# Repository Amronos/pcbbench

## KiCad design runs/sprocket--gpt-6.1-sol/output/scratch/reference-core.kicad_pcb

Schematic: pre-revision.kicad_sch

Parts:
C1, C18, C20: 1 µF; C_0402_1005Metric; MPN GRM155R61A105KE15D
C2, C6, C7, C9, C10, C11, C12, C13, C14, C15, C16, C17, C19, C25, C29, C33, C34: 100 nF; C_0402_1005Metric; MPN GRM155R71C104KA88D
C3, C4: 15 pF; C_0402_1005Metric; MPN GRM1555C1H150JA01D
C5, C21, C22, C31, C32: 4.7 µF; C_0603_1608Metric; MPN GRM188R61A475KE15D
C8: 4.7 µF; C_0402_1005Metric; MPN GRM155R60J475ME87D
C23, C24, C28, C30: 10 µF; C_0805_2012Metric; MPN GRM21BR61A106KE19L
C26, C27: 22 µF; C_0805_2012Metric; MPN GRM21BR60J226ME39L
D1: USB ESD; SOT-23-6; MPN USBLC6-2SC6
D2: RGB; LED_WS2812B-2020_PLCC4_2.0x2.0mm; MPN WS2812C-2020-V6
J1: USB-C; USB_C_Receptacle_HRO_TYPE-C-31-M-12; MPN TYPE-C-31-M-12
J2: microSD SPI; microSD_HC_Hirose_DM3AT-SF-PEJM5; MPN DM3AT-SF-PEJM5
J3: LiPo + NTC; JST_PH_S3B-PH-SM4-TB_1x03-1MP_P2.00mm_Horizontal; MPN S3B-PH-SM4-TB(LF)(SN)
J4: Qwiic / STEMMA QT; JST_SH_BM04B-SRSS-TB_1x04-1MP_P1.00mm_Vertical; MPN BM04B-SRSS-TB(LF)(SN)
J5: GPIO expansion; PinHeader_2x10_P2.54mm_Vertical; MPN 61302021121
J6: SWD; PinHeader_1x04_P2.54mm_Vertical; MPN 61300411121
L1: 2.2 µH; L_1812_4532Metric; MPN LQH44PN2R2MP0L
L2: 3.3 µH; L_Abracon_AOTA-B201610S; MPN AOTA-B201610S3R3-101-T
Q1: Battery sense gate; SOT-23; MPN BSS84
Q2: Sense enable; SOT-23; MPN 2N7002
R1, R2: 5.1 kΩ; R_0402_1005Metric; MPN RC0402FR-075K1L
R3, R4: 27 Ω; R_0402_1005Metric; MPN RC0402FR-0727RL
R5, R6, R8, R9, R10, R11, R12, R17, R18, R26, R27, R28, R29, R30, R31: 10 kΩ; R_0402_1005Metric; MPN RC0402FR-0710KL
R7, R25, R33, R34: 1 kΩ; R_0402_1005Metric; MPN RC0402FR-071KL
R13: 2.94 kΩ; R_0402_1005Metric; MPN RC0402FR-072K94L
R14: 3.83 kΩ; R_0402_1005Metric; MPN RC0402FR-073K83L
R15: 46.4 kΩ; R_0402_1005Metric; MPN RC0402FR-0746K4L
R16: 2.0 kΩ; R_0402_1005Metric; MPN RC0402FR-072KL
R19, R20, R23, R24, R35, R36: 100 kΩ; R_0402_1005Metric; MPN RC0402FR-07100KL
R21, R22: 4.7 kΩ; R_0402_1005Metric; MPN RC0402FR-074K7L
R32: 33 Ω; R_0402_1005Metric; MPN RC0402FR-0733RL
SW1: BOOT_SW; SW_SPST_B3U-1000P; MPN B3U-1000P
SW2: RUN; SW_SPST_B3U-1000P; MPN B3U-1000P
SW3: RADIO_BOOT; SW_SPST_B3U-1000P; MPN B3U-1000P
SW4: RADIO_EN; SW_SPST_B3U-1000P; MPN B3U-1000P
U1: RP2350A; QFN-60-1EP_7x7mm_P0.4mm_EP3.4x3.4mm; MPN RP2350A
U2: 16 MB QSPI; SOIC-8_5.3x5.3mm_P1.27mm; MPN W25Q128JVSIQ
U3: 8 MB PSRAM; SOIC-8_3.9x4.9mm_P1.27mm; MPN APS6404L-3SQR-SN
U4: BQ24074; VQFN-16-1EP_3x3mm_P0.5mm_EP1.6x1.6mm; MPN BQ24074RGTR
U5: 3.3 V buck-boost; Texas_DRC0010J; MPN TPS63001DRCR
U6: Wi-Fi + BLE; ESP32-C3-WROOM-02; MPN ESP32-C3-WROOM-02-N4
Y1: 12 MHz; Crystal_SMD_3225-4Pin_3.2x2.5mm; MPN ABM8-272-T3

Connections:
/1V1: C5.1, C6.1, C7.1, C8.1, L2.2, U1.6 (DVDD), U1.23 (DVDD), U1.39 (DVDD), U1.50 (VREG_FB)
/3V3: C9.1, C10.1, C11.1, C12.1, C13.1, C14.1, C15.1, C16.1, C17.1, C18.1, C19.1, C20.1, C26.1, C27.1, C28.1, C29.1, C30.1, C32.1, C33.1, D2.4 (VDD), J2.4 (VDD), J4.2, J5.1, J6.1, Q2.1 (G), R5.1, R6.1, R8.1, R9.1, R10.1, R11.1, R12.1, R17.1, R18.1, R21.1, R22.1, R26.1, R27.1, R28.1, R29.1, R30.1, R31.1, R32.1, R36.1, U1.1 (IOVDD), U1.11 (IOVDD), U1.20 (IOVDD), U1.30 (IOVDD), U1.38 (IOVDD), U1.44 (ADC_AVDD), U1.45 (IOVDD), U1.49 (VREG_VIN), U1.53 (USB_OTP_VDD), U1.54 (QSPI_IOVDD), U2.8 (VCC), U3.8 (VDD), U5.1 (VOUT), U5.10 (FB), U6.1 (3V3)
/BAT: C22.1, J3.1, Q1.2 (S), R35.1, U4.2 (BAT), U4.3 (BAT)
/BAT_ADC: C2.1, R23.2, R24.1, U1.40 (GPIO26/ADC0)
/BAT_GATE: Q1.1 (G), Q2.3 (D), R35.2
/BAT_NTC: J3.3, U4.1 (TS)
/BAT_SENSE: Q1.3 (D), R23.1
/BOOT_SW: R7.2, SW1.1
/CC1: J1.A5 (CC1), R1.1
/CC2: J1.B5 (CC2), R2.1
/CHG: J5.15, R17.2, U4.9 (~CHG)
/CORE_LX: L2.1, U1.48 (VREG_LX)
/FLASH_CS: R5.2, R7.1, U1.60 (~QSPI_SS), U2.1 (~CS)
/GND: C1.2, C2.2, C3.2, C4.2, C5.2, C6.2, C7.2, C8.2, C9.2, C10.2, C11.2, C12.2, C13.2, C14.2, C15.2, C16.2, C17.2, C18.2, C19.2, C20.2, C21.2, C22.2, C23.2, C24.2, C25.2, C26.2, C27.2, C28.2, C29.2, C30.2, C31.2, C32.2, C33.2, C34.2, D1.2 (GND), D2.2 (VSS), J1.A1 (GND), J1.A12 (GND), J1.B1 (GND), J1.B12 (GND), J1.SH (SHIELD), J2.6 (VSS), J2.10 (DET_A), J2.SH (SHIELD), J3.2, J4.1, J5.2, J5.20, J6.4, Q2.2 (S), R1.2, R2.2, R13.2, R14.2, R15.2, R16.2, R20.2, R24.2, R36.2, SW1.2, SW2.2, SW3.2, SW4.2, U1.47 (VREG_PGND), U1.61 (GND), U2.4 (GND), U3.4 (VSS), U4.4 (~CE), U4.5 (EN2), U4.8 (VSS), U4.17 (VSS), U5.3 (PGND), U5.7 (PS/SYNC), U5.9 (GND), U5.11 (PGND), U6.9 (GND), U6.19 (GND), Y1.2 (G), Y1.4 (G)
/GP1: J5.3, U1.3 (GPIO1)
/GP6: J5.4, U1.9 (GPIO6)
/GP7: J5.5, U1.10 (GPIO7)
/GP12: J5.11, U1.16 (GPIO12)
/GP13: J5.12, U1.17 (GPIO13)
/GP14: J5.13, U1.18 (GPIO14)
/GP15: J5.6, U1.19 (GPIO15)
/GP16: J5.7, U1.27 (GPIO16)
/GP17: J5.8, U1.28 (GPIO17)
/GP18: J5.9, U1.29 (GPIO18)
/GP19: J5.10, U1.31 (GPIO19)
/GP21: J5.16, U1.33 (GPIO21)
/GP22: J5.14, U1.34 (GPIO22)
/GP27: J5.17, U1.41 (GPIO27/ADC1)
/GP28: J5.18, U1.42 (GPIO28/ADC2)
/GP29: J5.19, U1.43 (GPIO29/ADC3)
/ILIM: R14.1, U4.12 (ILIM)
/ISET: R13.1, U4.16 (ISET)
/ITERM: R16.1, U4.15 (ITERM)
/PGOOD: R18.2, U4.7 (~PGOOD)
/PSRAM_CS: R6.2, U1.2 (GPIO0), U3.1 (~CE)
/PWR_L1: L1.1, U5.4 (L1)
/PWR_L2: L1.2, U5.2 (L2)
/QSPI_CLK: U1.56 (QSPI_SCLK), U2.6 (CLK), U3.6 (SCLK)
/QSPI_D0: U1.57 (QSPI_SD0), U2.5 (DI/IO_{0}), U3.5 (SI/SIO0)
/QSPI_D1: U1.59 (QSPI_SD1), U2.2 (DO/IO_{1}), U3.2 (SO/SIO1)
/QSPI_D2: U1.58 (QSPI_SD2), U2.3 (~WP/IO_{2}), U3.3 (SIO2)
/QSPI_D3: U1.55 (QSPI_SD3), U2.7 (~HOLD/~RESET/IO_{3}), U3.7 (SIO3)
/RADIO_BOOT: R10.2, R34.2, SW3.1, U6.8 (IO9)
/RADIO_BOOT_DRIVE: R34.1, U1.36 (GPIO24)
/RADIO_EN: C1.1, R9.2, R33.2, SW4.1, U6.2 (EN)
/RADIO_EN_DRIVE: R33.1, U1.35 (GPIO23)
/RADIO_IO2: R12.2, U6.16 (IO2)
/RADIO_IO8: R11.2, U6.7 (IO8)
/RADIO_RX: U1.7 (GPIO4), U6.11 (IO20/RXD)
/RADIO_TX: U1.8 (GPIO5), U6.12 (IO21/TXD)
/RGB_DATA: D2.3 (DIN), U1.32 (GPIO20)
/RUN: R8.2, SW2.1, U1.26 (RUN)
/SCL: J4.4, R22.2, U1.5 (GPIO3)
/SDA: J4.3, R21.2, U1.4 (GPIO2)
/SD_CLK: J2.5 (CLK), U1.14 (GPIO10)
/SD_CS: J2.2 (DAT3/CD), R26.2, U1.13 (GPIO9)
/SD_DAT1: J2.8 (DAT1), R29.2
/SD_DAT2: J2.1 (DAT2), R30.2
/SD_DETECT: J2.9 (DET_B), R31.2, U1.37 (GPIO25)
/SD_MISO: J2.7 (DAT0), R28.2, U1.12 (GPIO8)
/SD_MOSI: J2.3 (CMD), R27.2, U1.15 (GPIO11)
/SWCLK: J6.3, U1.24 (SWCLK)
/SWDIO: J6.2, U1.25 (SWDIO)
/SYS: C23.1, C24.1, C25.1, U4.10 (OUT), U4.11 (OUT), U5.5 (VIN), U5.6 (EN), U5.8 (VINA)
/TMR: R15.1, U4.14 (TMR)
/USB_CONN_DM: D1.3 (I/O2), D1.4 (I/O2), J1.A7 (D-), J1.B7 (D-), R4.1
/USB_CONN_DP: D1.1 (I/O1), D1.6 (I/O1), J1.A6 (D+), J1.B6 (D+), R3.1
/USB_DM: R4.2, U1.51 (USB_DM)
/USB_DP: R3.2, U1.52 (USB_DP)
/USB_LIMIT: R19.2, R20.1, U4.6 (EN1)
/VBUS: C21.1, C34.1, D1.5 (VBUS), J1.A4 (VBUS), J1.A9 (VBUS), J1.B4 (VBUS), J1.B9 (VBUS), R19.1, U4.13 (IN)
/VREG_AVDD: C31.1, R32.2, U1.46 (VREG_AVDD)
/XIN: C3.1, U1.21 (XIN), Y1.1
/XOUT: R25.2, U1.22 (XOUT)
/XTAL_OUT: C4.1, R25.1, Y1.3

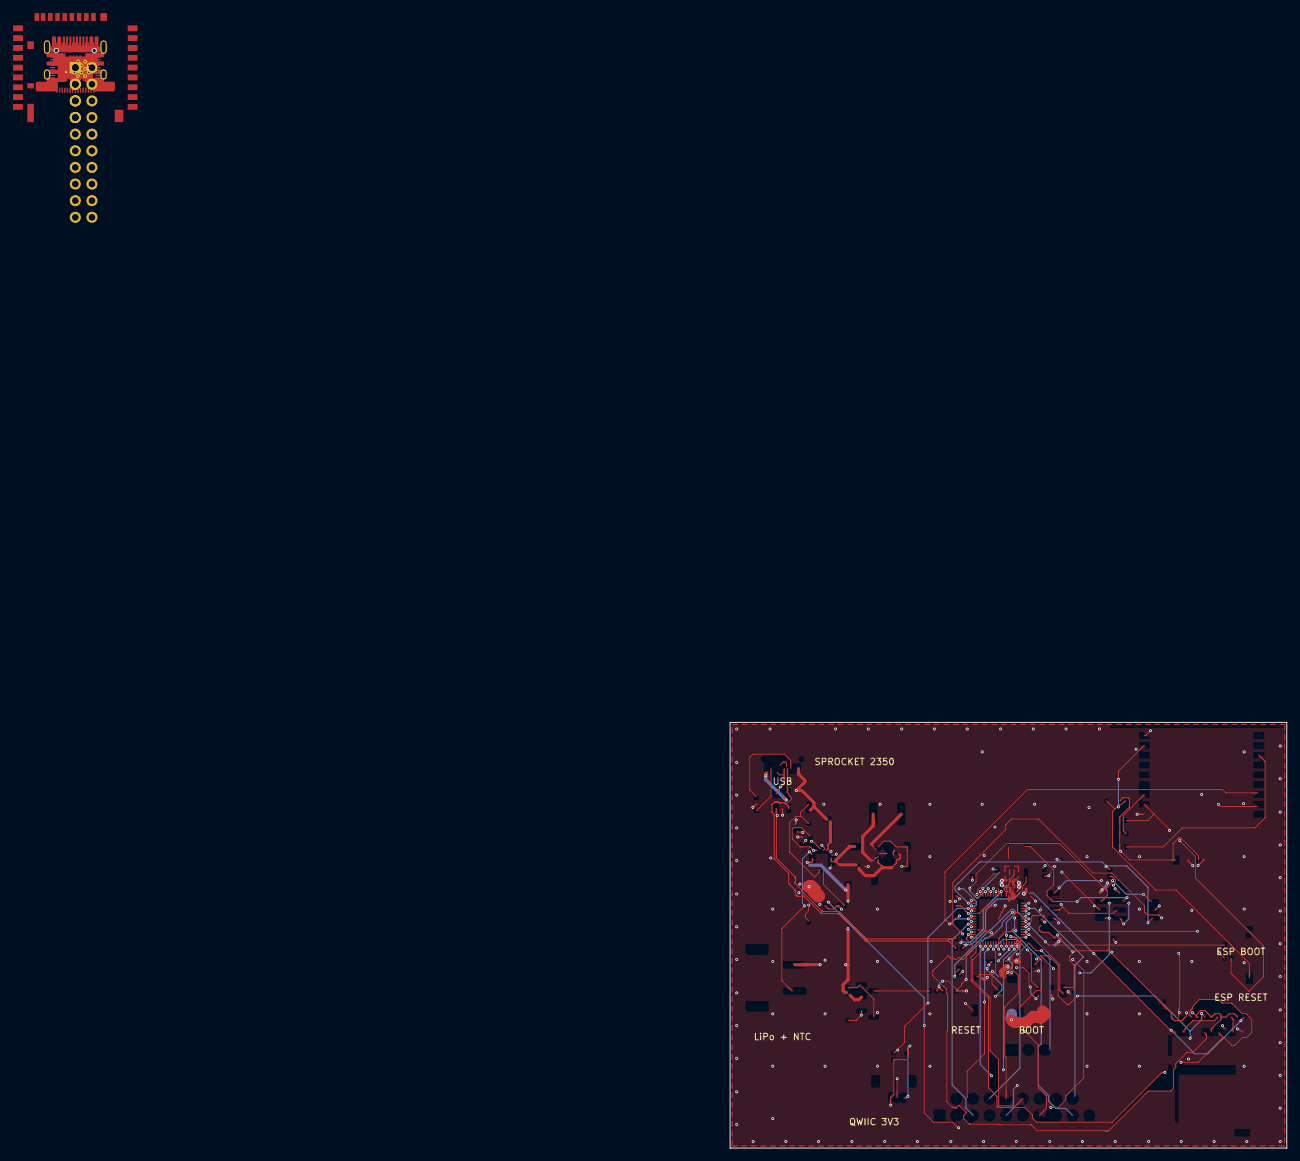
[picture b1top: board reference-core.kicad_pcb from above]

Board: 4 copper layers, 85.0 x 65.0 mm, 93 parts (0 on the bottom side), 75 nets.

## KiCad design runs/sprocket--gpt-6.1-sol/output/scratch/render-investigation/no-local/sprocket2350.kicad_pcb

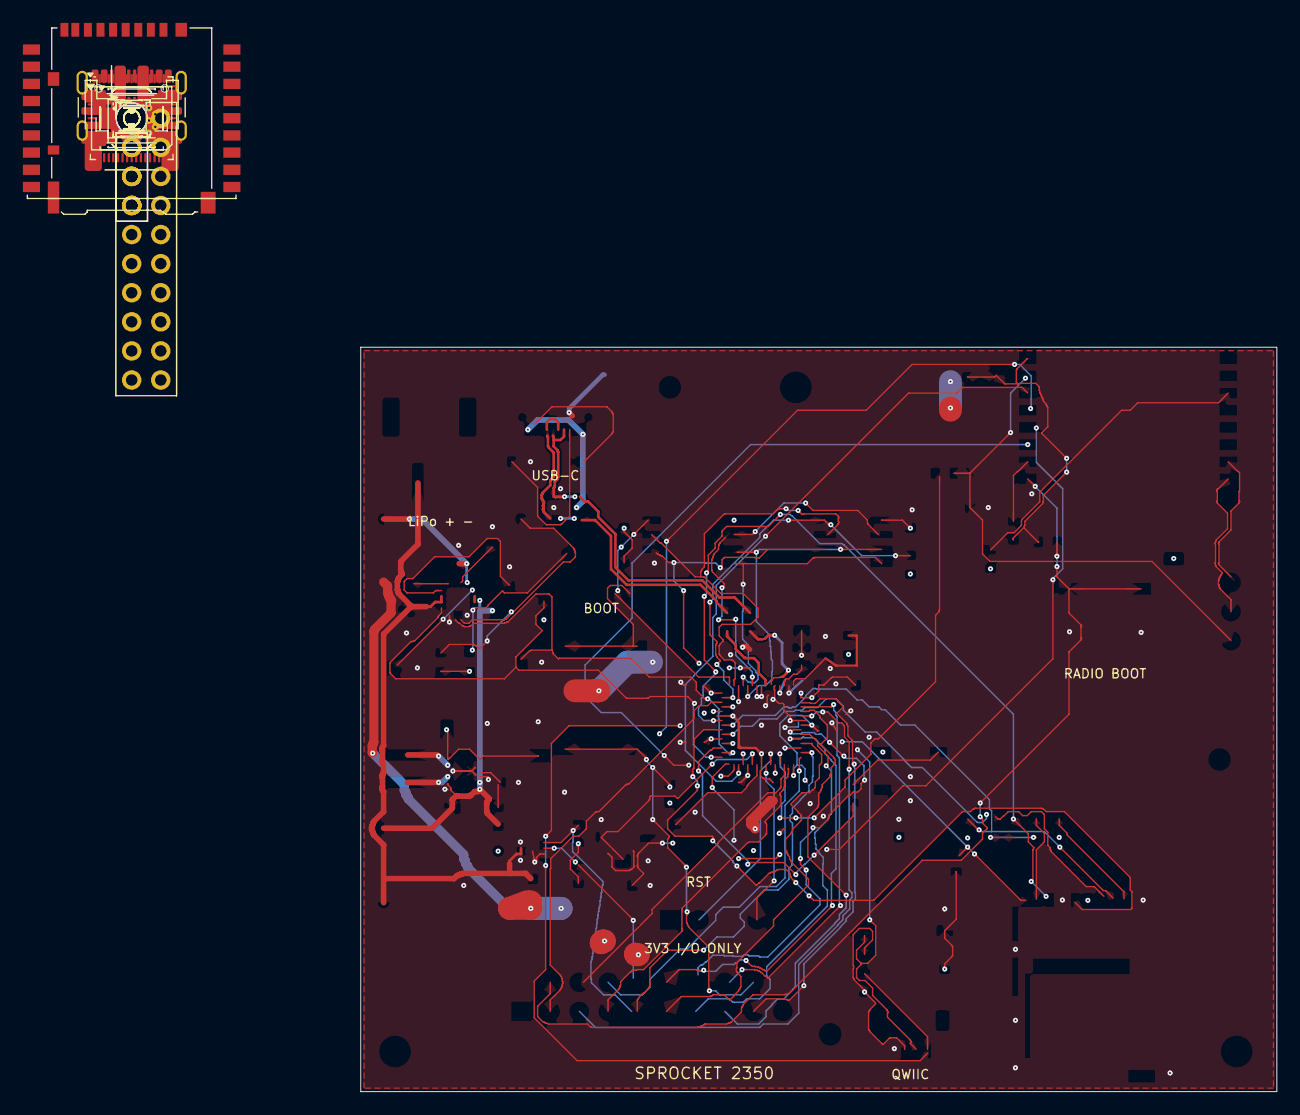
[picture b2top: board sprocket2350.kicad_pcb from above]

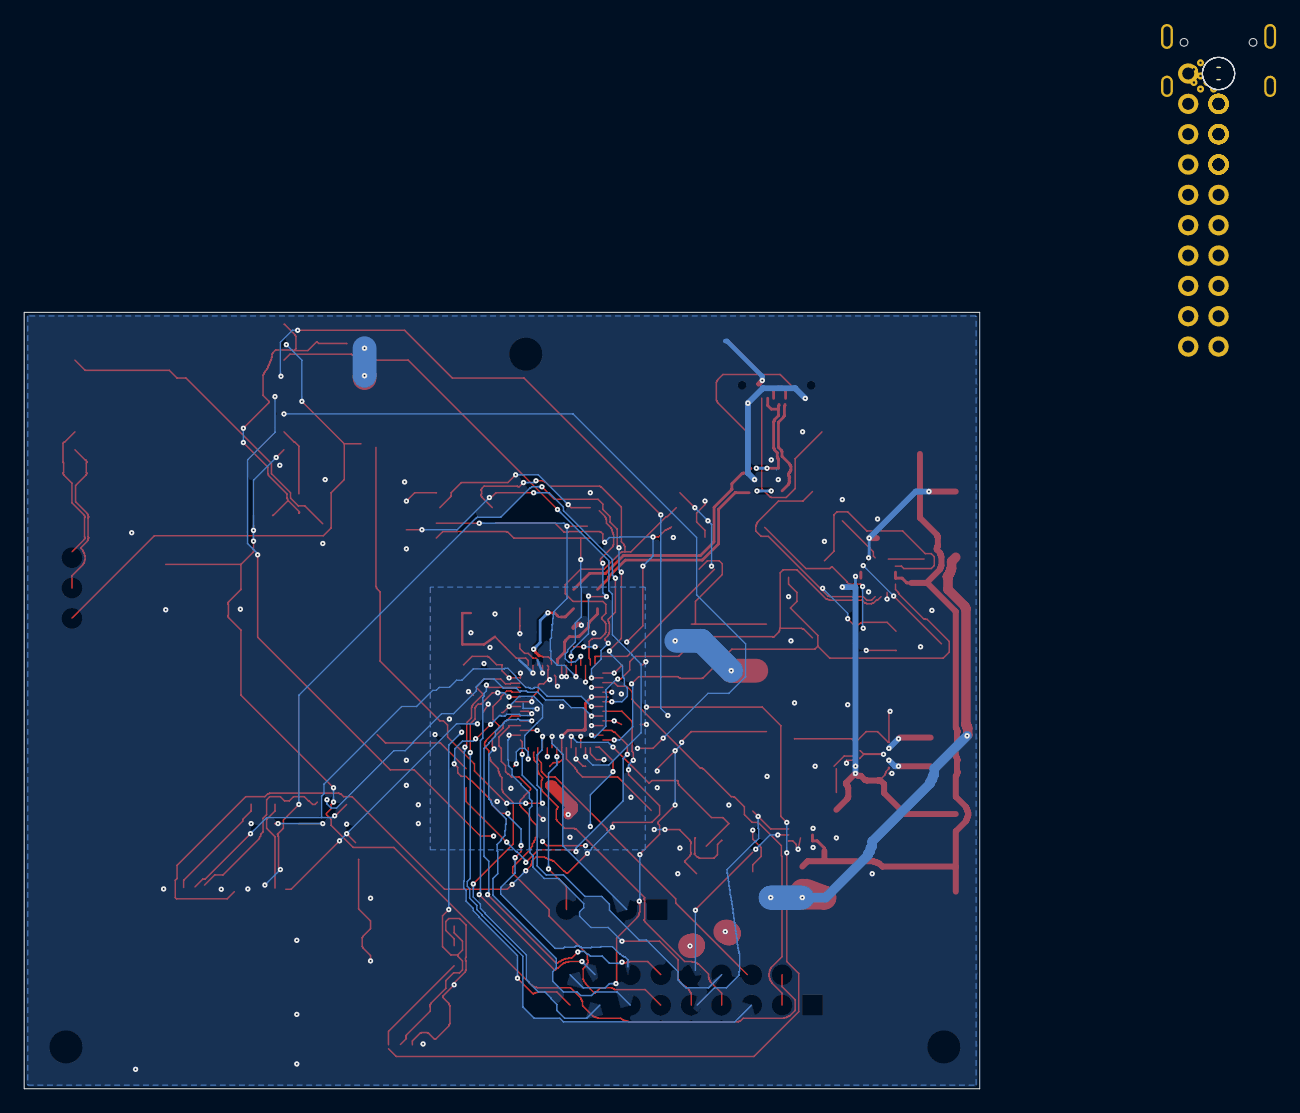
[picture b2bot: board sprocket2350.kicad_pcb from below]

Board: 4 copper layers, 80.0 x 65.0 mm, 106 parts (2 on the bottom side), 75 nets.

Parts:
C1, C2, C9, C10, C11, C12, C13, C14, C15, C16, C17, C18, C19, C25, C28, C31, C34, C35: 100 nF; C_0603_1608Metric
C3, C4: 15 pF; C_0603_1608Metric
C5, C7, C8: 4.7 µF; C_0805_2012Metric
C6: 4.7 µF; C_0603_1608Metric
C20: 100 nF; C_0201_0603Metric
C21, C29: 1 µF; C_0603_1608Metric
C22, C23, C24, C30, C33: 10 µF; C_0805_2012Metric
C26, C27, C32: 22 µF; C_1206_3216Metric
D1: RGB V6; LED_WS2812B_PLCC4_5.0x5.0mm_P3.2mm
FID1, FID2, FID3: Fiducial; Fiducial_1mm_Mask2mm
H1, H2, H3: M2.5; MountingHole_2.7mm_M2.5
J1: USB-C; USB_C_Receptacle_GCT_USB4105-xx-A_16P_TopMnt_Horizontal
J2: LiPo; JST_PH_S2B-PH-SM4-TB_1x02-1MP_P2.00mm_Horizontal
J3: Radio UART; PinHeader_1x04_P2.54mm_Vertical
J4: microSD; microSD_HC_Hirose_DM3AT-SF-PEJM5
J5: Qwiic / STEMMA QT; JST_SH_BM04B-SRSS-TB_1x04-1MP_P1.00mm_Vertical
J6: GPIO; PinHeader_2x10_P2.54mm_Vertical
J7: SWD; PinHeader_1x04_P2.54mm_Vertical
L1: 3.3 µH; L_Abracon_AOTA-B201610S
L2: 2.2 µH; L_Coilcraft_XxL4020
R1, R4, R13, R16, R17, R18, R19, R23, R24, R25, R26, R27, R28, R29, R30, R31: 10 kΩ; R_0603_1608Metric
R2: 1.8 kΩ; R_0603_1608Metric
R3, R5, R35: 1 kΩ; R_0603_1608Metric
R6: 33 Ω; R_0603_1608Metric
R7, R8, R32, R33: 5.1 kΩ; R_0603_1608Metric
R9, R10: 27 Ω; R_0603_1608Metric
R11: 8.66 kΩ; R_0603_1608Metric
R12: 3.48 kΩ; R_0603_1608Metric
R14: 68.1 kΩ; R_0603_1608Metric
R20, R21: 3.3 kΩ; R_0603_1608Metric
R22: 100 kΩ; R_0603_1608Metric
R34: 330 Ω; R_0603_1608Metric
R36: 100 Ω; R_0603_1608Metric
SW1: BOOT; SW_SPST_TL3342
SW2: RESET; SW_SPST_TL3342
SW3: RADIO BOOT; SW_SPST_TL3342
TP1: VBUS; TestPoint_Pad_D1.0mm
TP2: SYS; TestPoint_Pad_D1.0mm
TP3: +3V3; TestPoint_Pad_D1.0mm
TP4: GND; TestPoint_Pad_D1.0mm
TP5: BAT; TestPoint_Pad_D1.0mm
TP6: CHG_N; TestPoint_Pad_D1.0mm
TP7: USB_PGOOD_N; TestPoint_Pad_D1.0mm
TP8: CORE_1V1; TestPoint_Pad_D1.0mm
U1: RP2350A; QFN-60-1EP_7x7mm_P0.4mm_EP3.4x3.4mm
U2: 16 MB flash; SOIC-8_5.3x5.3mm_P1.27mm
U3: 8 MB PSRAM; SOIC-8_3.9x4.9mm_P1.27mm
U4: USB ESD; SOT-23-6
U5: Power-path charger; VQFN-16-1EP_3x3mm_P0.5mm_EP1.6x1.6mm
U6: 3.3 V buck-boost; Texas_DRC0010J
U7: Wi-Fi + BLE; ESP32-C3-WROOM-02
U8: Battery voltage / SOC; TDFN-8-1EP_2x2mm_P0.5mm_EP0.8x1.2mm
Y1: 12 MHz; Crystal_SMD_3225-4Pin_3.2x2.5mm

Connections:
/+3V3: C1.1, C2.1, C6.1, C9.1, C10.1, C11.1, C12.1, C13.1, C14.1, C15.1, C16.1, C17.1, C26.1, C27.1, C30.1, C31.1, C32.1, C33.1, C34.1, C35.1, D1.1 (VDD), J4.4 (VDD), J5.2, J6.1, J6.19, J7.1, R1.1, R2.1, R4.1, R6.1, R17.1, R18.1, R19.1, R20.1, R21.1, R23.1, R24.1, R25.1, R26.1, R27.1, R28.1, R29.1, R30.1, R31.1, R32.1, R33.1, TP3.1 (1_1), U1.1 (IOVDD), U1.11 (IOVDD), U1.20 (IOVDD), U1.30 (IOVDD), U1.38 (IOVDD), U1.44 (ADC_AVDD), U1.45 (IOVDD), U1.49 (VREG_VIN), U1.53 (USB_OTP_VDD), U1.54 (QSPI_IOVDD), U2.8 (VCC), U3.8 (VDD), U6.1 (VOUT), U6.10 (FB), U7.1 (3V3)
/ADC0: J6.5, U1.40 (GPIO26/ADC0)
/ADC1: J6.15, U1.41 (GPIO27/ADC1)
/ADC2: J6.16, U1.42 (GPIO28/ADC2)
/ADC3: J6.17, U1.43 (GPIO29/ADC3)
/BAT: C22.1, C28.1, J2.2, TP5.1 (1_1), U5.2 (BAT), U5.3 (BAT), U8.2 (CELL), U8.3 (VDD)
/BAT_TS: R13.1, U5.1 (TS)
/BOOT_SWITCH: R3.2, SW1.1
/BUCK_L1: L2.1, U6.4 (L1)
/BUCK_L2: L2.2, U6.2 (L2)
/BUCK_VINA: C25.1, R36.2, U6.8 (VINA)
/CC1: J1.A5 (CC1), R7.1
/CC2: J1.B5 (CC2), R8.1
/CHARGE_DISABLE: R17.2, U1.15 (GPIO11), U5.4 (~CE)
/CHG_ILIM: R12.1, U5.12 (ILIM)
/CHG_ISET: R11.1, U5.16 (ISET)
/CHG_N: R19.2, TP6.1 (1_1), U5.9 (~CHG)
/CHG_TMR: R14.1, U5.14 (TMR)
/CORE_1V1: C7.1, C8.1, C18.1, C19.1, C20.1, L1.1, TP8.1 (1_1), U1.6 (DVDD), U1.23 (DVDD), U1.39 (DVDD), U1.50 (VREG_FB)
/FLASH_CS: R1.2, R3.1, U1.60 (~QSPI_SS), U2.1 (~CS)
/GAUGE_SCL: J6.10, R21.2, U1.33 (GPIO21), U8.7 (SCL)
/GAUGE_SDA: J6.9, R20.2, U1.32 (GPIO20), U8.8 (SDA)
/GND: C1.2, C2.2, C3.2, C4.2, C5.2, C6.2, C7.2, C8.2, C9.2, C10.2, C11.2, C12.2, C13.2, C14.2, C15.2, C16.2, C17.2, C18.2, C19.2, C20.2, C21.2, C22.2, C23.2, C24.2, C25.2, C26.2, C27.2, C28.2, C29.2, C30.2, C31.2, C32.2, C33.2, C34.2, C35.2, D1.3 (VSS), J1.A1 (GND), J1.A12 (GND), J1.B1 (GND), J1.B12 (GND), J1.SH (SHIELD), J2.1, J3.1, J4.6 (VSS), J4.10 (DET_A), J4.SH (SHIELD), J5.1, J6.2, J6.20, J7.3, R7.2, R8.2, R11.2, R12.2, R13.2, R14.2, R16.2, R22.2, SW1.2, SW2.2, SW3.2, TP4.1 (1_1), U1.47 (VREG_PGND), U1.61 (GND), U2.4 (GND), U3.4 (VSS), U4.2 (GND), U5.5 (EN2), U5.8 (VSS), U5.17 (VSS), U6.3 (PGND), U6.7 (PS/SYNC), U6.9 (GND), U6.11 (PGND), U7.9 (GND), U7.19 (GND), U8.1 (CTG), U8.4 (GND), U8.6 (QSTRT), U8.9 (EP), Y1.2 (G), Y1.4 (G)
/GPIO1: J6.3, U1.3 (GPIO1)
/GPIO17: J6.6, U1.28 (GPIO17)
/GPIO18: J6.7, U1.29 (GPIO18)
/GPIO19: J6.8, U1.31 (GPIO19)
/GPIO22: J6.11, U1.34 (GPIO22)
/GPIO23: J6.12, U1.35 (GPIO23)
/GPIO24: J6.13, U1.36 (GPIO24)
/GPIO25: J6.14, U1.37 (GPIO25)
/I2C_SCL: J5.4, R33.2, U1.5 (GPIO3)
/I2C_SDA: J5.3, R32.2, U1.4 (GPIO2)
/MCU_USB_N: R10.2, U1.51 (USB_DM)
/MCU_USB_P: R9.2, U1.52 (USB_DP)
/PROG_RX: J3.3, U7.11 (IO20/RXD)
/PROG_TX: J3.2, U7.12 (IO21/TXD)
/PSRAM_CS: R2.2, U1.2 (GPIO0), U3.1 (~CE)
/QSPI_CLK: U1.56 (QSPI_SCLK), U2.6 (CLK), U3.6 (SCLK)
/QSPI_D0: U1.57 (QSPI_SD0), U2.5 (DI/IO_{0}), U3.5 (SI/SIO0)
/QSPI_D1: U1.59 (QSPI_SD1), U2.2 (DO/IO_{1}), U3.2 (SO/SIO1)
/QSPI_D2: U1.58 (QSPI_SD2), U2.3 (~WP/IO_{2}), U3.3 (SIO2)
/QSPI_D3: U1.55 (QSPI_SD3), U2.7 (~HOLD/~RESET/IO_{3}), U3.7 (SIO3)
/RADIO_BOOT: J6.4, R24.2, SW3.1, U7.8 (IO9)
/RADIO_CTRL: R35.1, U1.27 (GPIO16)
/RADIO_EN: C29.1, J3.4, R22.1, R35.2, U7.2 (EN)
/RADIO_IO2: R25.2, U7.16 (IO2)
/RADIO_IO8: R23.2, U7.7 (IO8)
/RGB_DATA: R34.1, U1.13 (GPIO9)
/RGB_DIN: D1.4 (DIN), R34.2
/RUN: J6.18, R4.2, SW2.1, U1.26 (RUN)
/SD_CLK: J4.5 (CLK), U1.9 (GPIO6)
/SD_CS: J4.2 (DAT3/CD), R26.2, U1.8 (GPIO5)
/SD_DAT1: J4.8 (DAT1), R29.2
/SD_DAT2: J4.1 (DAT2), R30.2
/SD_DETECT: J4.9 (DET_B), R31.2, U1.12 (GPIO8)
/SD_MISO: J4.7 (DAT0), R28.2, U1.7 (GPIO4)
/SD_MOSI: J4.3 (CMD), R27.2, U1.10 (GPIO7)
/SWCLK: J7.4, U1.24 (SWCLK)
/SWDIO: J7.2, U1.25 (SWDIO)
/SYS: C23.1, C24.1, R36.1, TP2.1 (1_1), U5.10 (OUT), U5.11 (OUT), U6.5 (VIN), U6.6 (EN)
/UART_CTS: U1.18 (GPIO14), U7.3 (IO4)
/UART_RTS: U1.19 (GPIO15), U7.4 (IO5)
/UART_RX: U1.17 (GPIO13), U7.6 (IO7)
/UART_TX: U1.16 (GPIO12), U7.5 (IO6)
/USB_500_EN: R16.1, U1.14 (GPIO10), U5.6 (EN1)
/USB_D_N: J1.A7 (D-), J1.B7 (D-), R10.1, U4.1 (I/O1), U4.6 (I/O1)
/USB_D_P: J1.A6 (D+), J1.B6 (D+), R9.1, U4.3 (I/O2), U4.4 (I/O2)
/USB_PGOOD_N: R18.2, TP7.1 (1_1), U5.7 (~PGOOD)
/VBUS: C21.1, J1.A4 (VBUS), J1.A9 (VBUS), J1.B4 (VBUS), J1.B9 (VBUS), TP1.1 (1_1), U4.5 (VBUS), U5.13 (IN)
/VREG_AVDD: C5.1, R6.2, U1.46 (VREG_AVDD)
/VREG_LX: L1.2, U1.48 (VREG_LX)
/XIN: C3.1, U1.21 (XIN), Y1.1
/XOUT: R5.1, U1.22 (XOUT)
/XTAL_OUT: C4.1, R5.2, Y1.3
